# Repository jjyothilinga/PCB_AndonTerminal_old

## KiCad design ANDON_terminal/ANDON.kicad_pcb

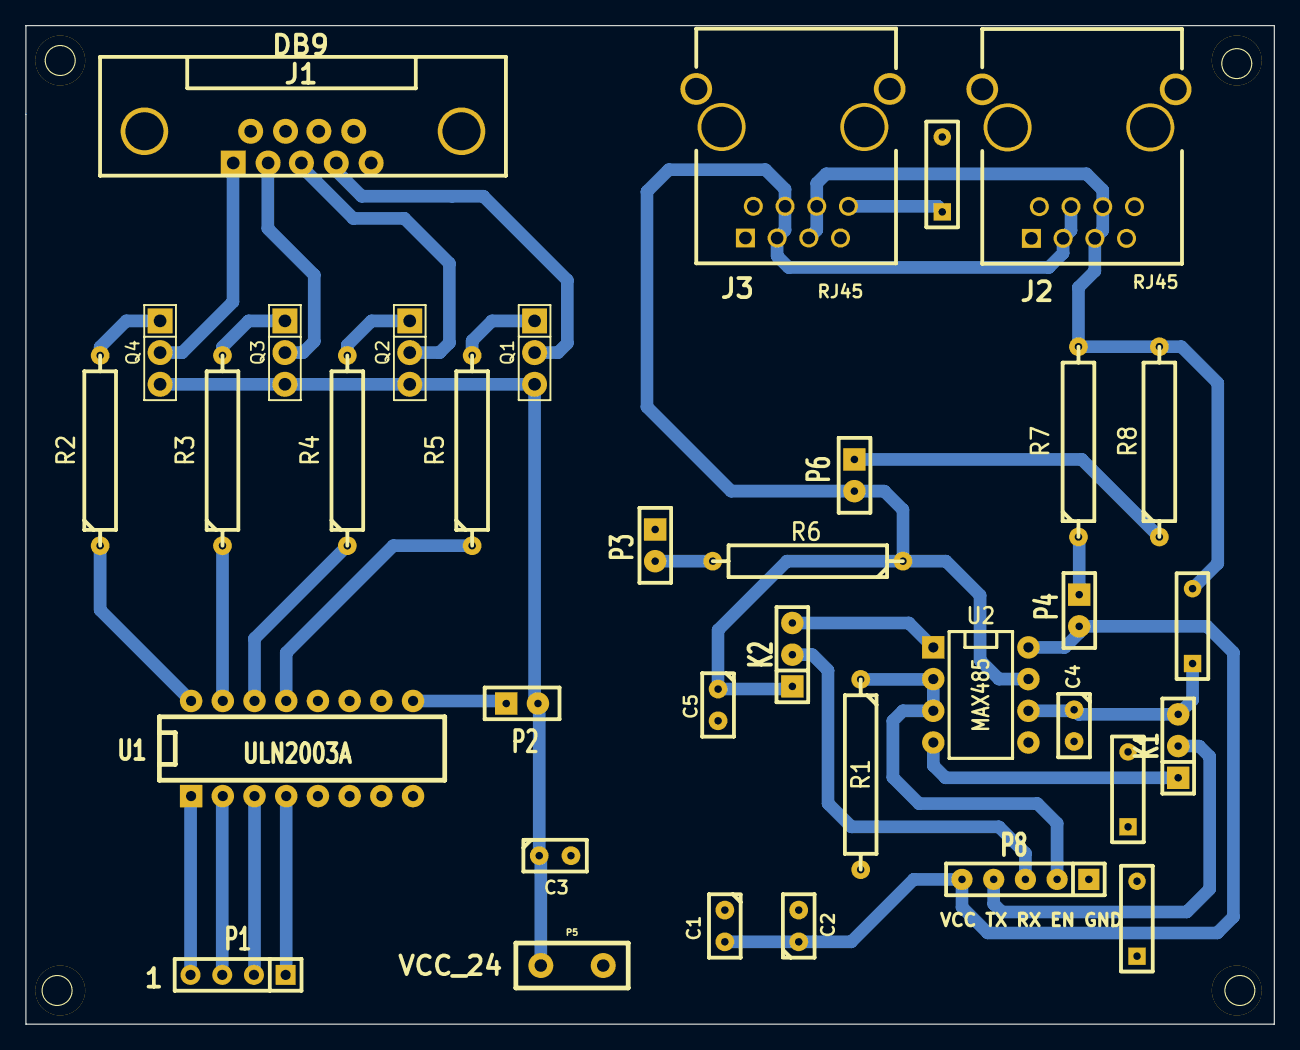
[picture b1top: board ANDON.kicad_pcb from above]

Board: 2 copper layers, 100.0 x 80.0 mm, 30 parts (0 on the bottom side), 31 nets.

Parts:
C1, C2: 0.1uF; Ideonics_Ceramic
C3: 104; Ideonics_Ceramic
C4, C5: 100pF; Ideonics_Ceramic
J1: DB9; Ideonics_DB9FC
J2, J3: RJ45; Ideonics_RJ45
K1, K2: CONN_3; Ideonics_RMC_3
P1: Ideonics_RMC_4Pin
P2, P3, P4: Ideonics_RMC_2
P6: CONN_2; Ideonics_RMC_2
P8: Ideonics_RMC_5
Q1, Q2, Q3, Q4: TIP127; Ideonics_TIP127
R1: R; Ideonics_R
R2, R3, R4, R5: 2.2K; Ideonics_R
R6, R7, R8: 470; Ideonics_R
U1: ULN2003A; Idenoics_ULN2003
U2: MAX485; Ideonics_MAX485

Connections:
/RS485_A_1: C4.1, K1.3, U2.6
/RS485_A_2: J2.5, J2.6, J3.5, J3.6, R7.2, R8.2
/RS485_B: C5.1, J2.3, J2.4, J3.3, J3.4, K2.1, P6.2, R6.1, U2.7
/RX: K2.3, U2.1
/SER_RX: K2.2, P8.3
/SER_TX: K1.2, P8.4
/TX: K1.1, U2.4
/TX_EN: P8.2, R1.1, U2.2, U2.3
/ULN1: Q4.1, R2.2
/ULN2: Q3.1, R3.2
/ULN3: Q2.1, R4.2
/ULN4: Q1.1, R5.2
/VCC_24V: C3.1, P2.2, Q1.3, Q2.3, Q3.3, Q4.3
GND: C1.1, C2.2, C3.2, C4.2, C5.2, J1.5, J2.8, P3.1, P8.1, R1.2, U1.8, U2.5
unnamed: P2.1, U1.9
unnamed: J1.4, Q1.2
unnamed: J1.3, Q2.2
unnamed: J1.2, Q3.2
unnamed: J1.1, Q4.2
unnamed: P1.1, U1.4
unnamed: P1.2, U1.3
unnamed: P1.3, U1.2
unnamed: P1.4, U1.1
unnamed: P6.1, R8.1
unnamed: R2.1, U1.16
unnamed: R5.1, U1.13
unnamed: R4.1, U1.14
unnamed: R3.1, U1.15
unnamed: P3.2, R6.2
unnamed: P4.1, R7.1
VCC: C1.2, C2.1, P4.2, P8.5, U2.8

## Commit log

2015-05-30 :space_invader: Added .gitattributes & .gitignore files
2015-05-30 Project creation
